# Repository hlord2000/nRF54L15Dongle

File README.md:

# nRF54L15 Dongle

High-performance BLE development dongle featuring Nordic's nRF54L15 SoC with integrated nRF52833-based debugger.

## Hardware

- nRF54L15 SoC with BLE 6.0 and 4Mbps proprietary PHY
- Integrated nRF52833 as pyOCD debugger and UART-USB bridge
- USB Type-C plug for direct computer connection
- RGB LED and dual buttons (reset + user/bootloader)

## Features

- Onboard debugging eliminates external tools
- Concurrent debug and serial bridge operation
- High-throughput 4Mbps proprietary radio mode
- Compact plug-in form factor

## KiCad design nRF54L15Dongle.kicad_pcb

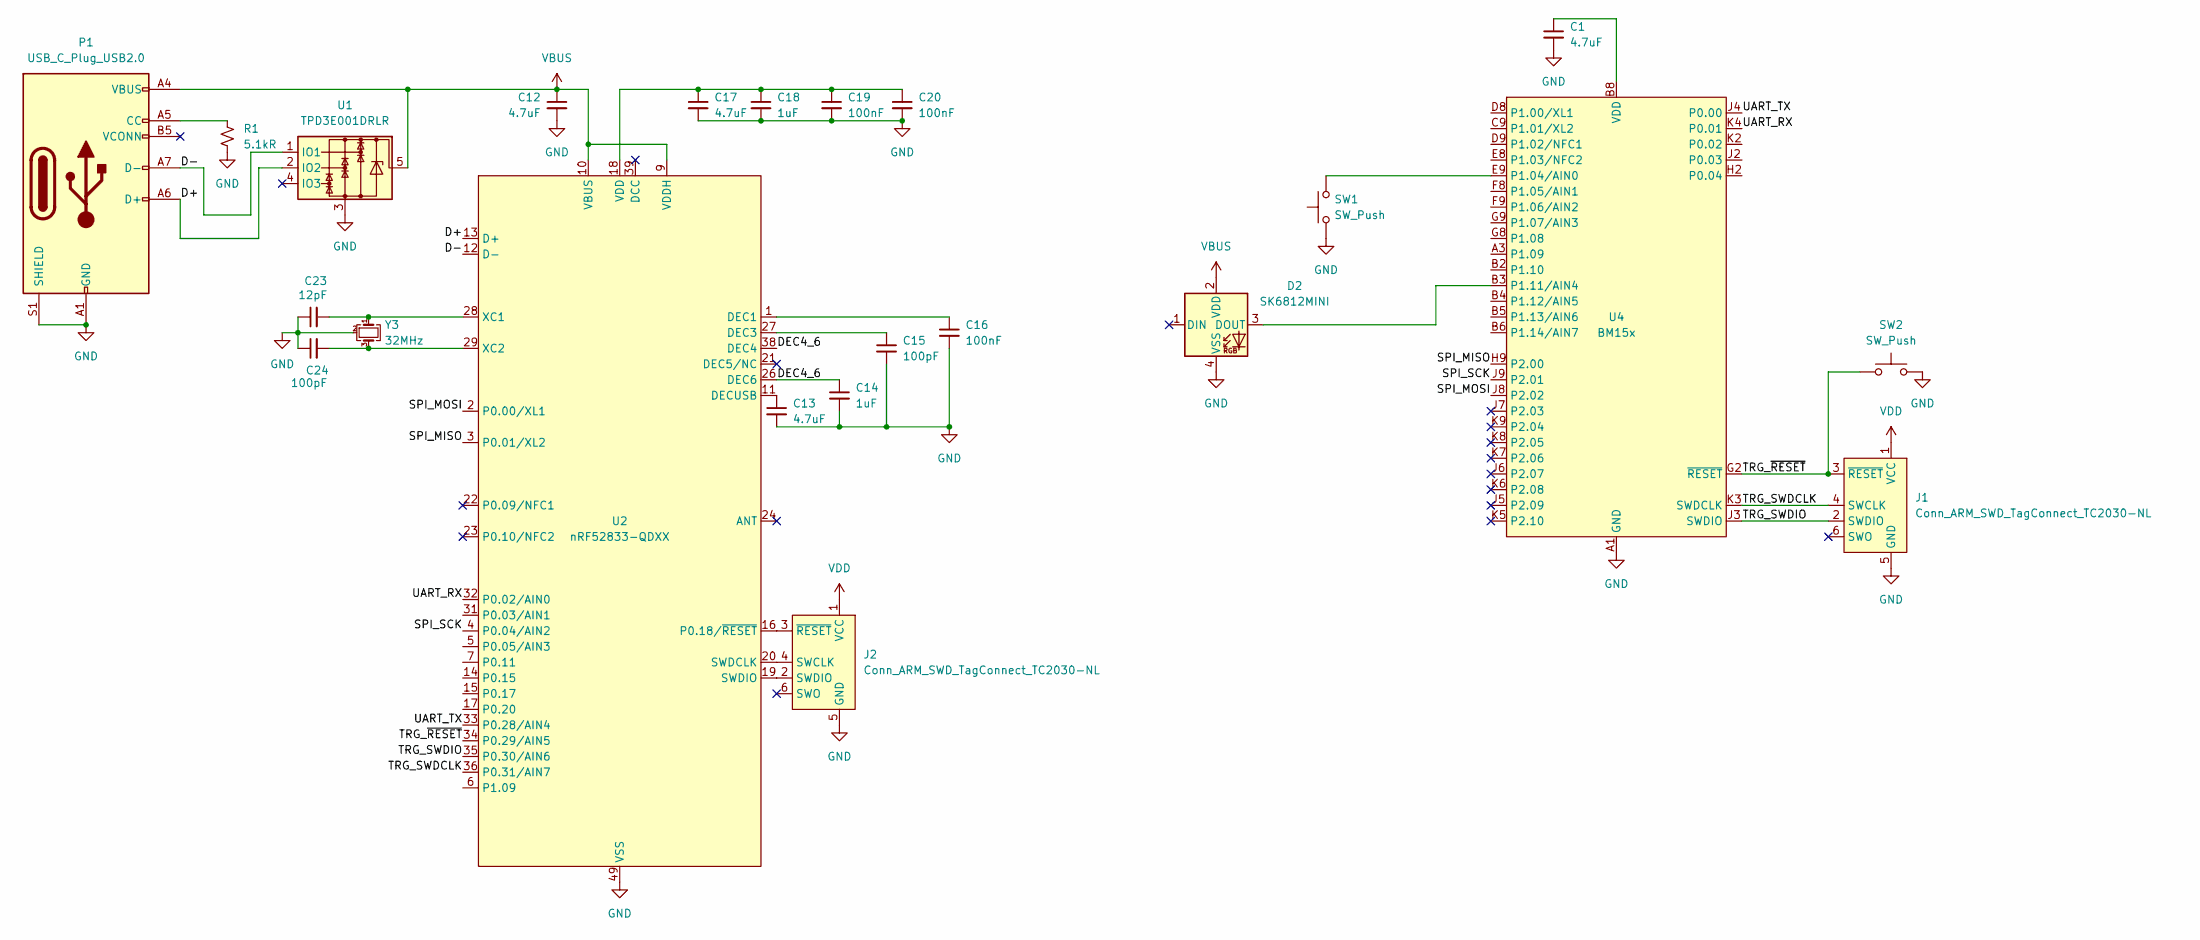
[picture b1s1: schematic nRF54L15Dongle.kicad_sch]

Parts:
C1, C12, C13, C17: 4.7uF; C_0402_1005Metric
C14, C18: 1uF; C_0201_0603Metric
C15, C24: 100pF; C_0201_0603Metric
C16, C19, C20: 100nF; C_0201_0603Metric
C23: 12pF; C_0201_0603Metric
D2: SK6812MINI; LED_SK6812_EC15_1.5x1.5mm; LCSC C2890035
J1, J2: Conn_ARM_SWD_TagConnect_TC2030-NL; Tag-Connect_TC2030-IDC-NL_2x03_P1.27mm_Vertical
P1: USB_C_Plug_USB2.0; USB_C_Plug_Molex_105444; LCSC C134082
R1: 5.1kR; R_0201_0603Metric
SW1, SW2: SW_Push; SW_Push_1P1T_NO_Vertical_Wuerth_434133025816
U1: TPD3E001DRLR; SOT-553
U2: nRF52833-QDXX; QFN-40-1EP_5x5mm_P0.4mm_EP3.6x3.6mm
U4: BM15x; BM15x-LGA-45_15.8x10mm
Y3: 32MHz; Crystal_SMD_2016-4Pin_2.0x1.6mm

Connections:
/D+: P1.A6 (D+), U1.2 (IO2), U2.13 (D+)
/D-: P1.A7 (D-), U1.1 (IO1), U2.12 (D-)
/DEC4_6: C14.1, U2.26 (DEC6), U2.38 (DEC4)
/SPI_MISO: U2.3 (P0.01/XL2), U4.H9 (P2.00)
/SPI_MOSI: U2.2 (P0.00/XL1), U4.J8 (P2.02)
/SPI_SCK: U2.4 (P0.04/AIN2), U4.J9 (P2.01)
/TRG_SWDCLK: J1.4 (SWCLK), U2.36 (P0.31/AIN7), U4.K3 (SWDCLK)
/TRG_SWDIO: J1.2 (SWDIO), U2.35 (P0.30/AIN6), U4.J3 (SWDIO)
/TRG_~RESET: J1.3 (~RESET), SW2.1, U2.34 (P0.29/AIN5), U4.G2 (~RESET)
/UART_RX: U2.32 (P0.02/AIN0), U4.K4 (P0.01)
/UART_TX: U2.33 (P0.28/AIN4), U4.J4 (P0.00)
GND: C1.2, C12.2, C13.2, C14.2, C15.2, C16.2, C17.2, C18.2, C19.2, C20.2, C23.1, C24.1, D2.4 (VSS), J1.5 (GND), J2.5 (GND), P1.A1 (GND), P1.A12 (GND), P1.B1 (GND), P1.B12 (GND), P1.S1 (SHIELD), R1.2, SW1.1, SW2.2, U1.3, U2.25 (VSS_PA), U2.37 (VSS), U2.49 (VSS), U4.A1 (GND), U4.A9 (GND), U4.B1 (GND), U4.B7 (GND), U4.B9 (GND), U4.D1 (GND), U4.E1 (GND), U4.F1 (GND), U4.H8 (GND), Y3.2, Y3.4
unnamed: C1.1, U4.B8 (VDD), U4.C8 (VDD)
unnamed: C17.1, C18.1, C19.1, C20.1, U2.8 (VDD), U2.18 (VDD), U2.30 (VDD), U2.40 (VDD)
unnamed: D2.3 (DOUT), U4.B3 (P1.11/AIN4)
unnamed: J2.4 (SWCLK), U2.20 (SWDCLK)
unnamed: J2.2 (SWDIO), U2.19 (SWDIO)
unnamed: J2.3 (~RESET), U2.16 (P0.18/~RESET)
unnamed: P1.A5 (CC), R1.1
unnamed: C16.1, U2.1 (DEC1)
unnamed: C15.1, U2.27 (DEC3)
unnamed: C13.1, U2.11 (DECUSB)
unnamed: C23.2, U2.28 (XC1), Y3.1
unnamed: C24.2, U2.29 (XC2), Y3.3
unnamed: SW1.2, U4.E9 (P1.04/AIN0)
VBUS: C12.1, D2.2 (VDD), P1.A4 (VBUS), P1.A9 (VBUS), P1.B4 (VBUS), P1.B9 (VBUS), U1.5, U2.9 (VDDH), U2.10 (VBUS)
VDD: J1.1 (VCC), J2.1 (VCC)

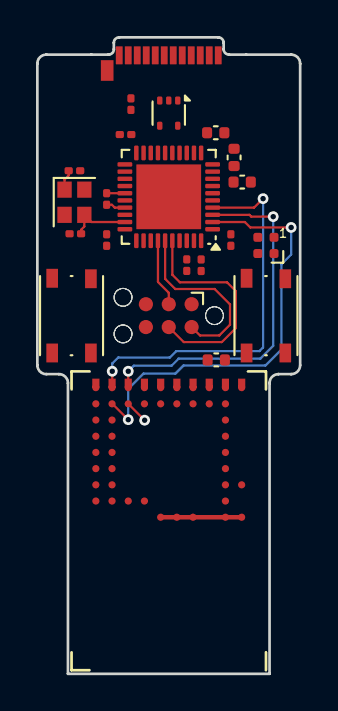
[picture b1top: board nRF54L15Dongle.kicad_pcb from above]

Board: 6 copper layers, 14.6 x 35.4 mm, 23 parts (1 on the bottom side), 27 nets.
